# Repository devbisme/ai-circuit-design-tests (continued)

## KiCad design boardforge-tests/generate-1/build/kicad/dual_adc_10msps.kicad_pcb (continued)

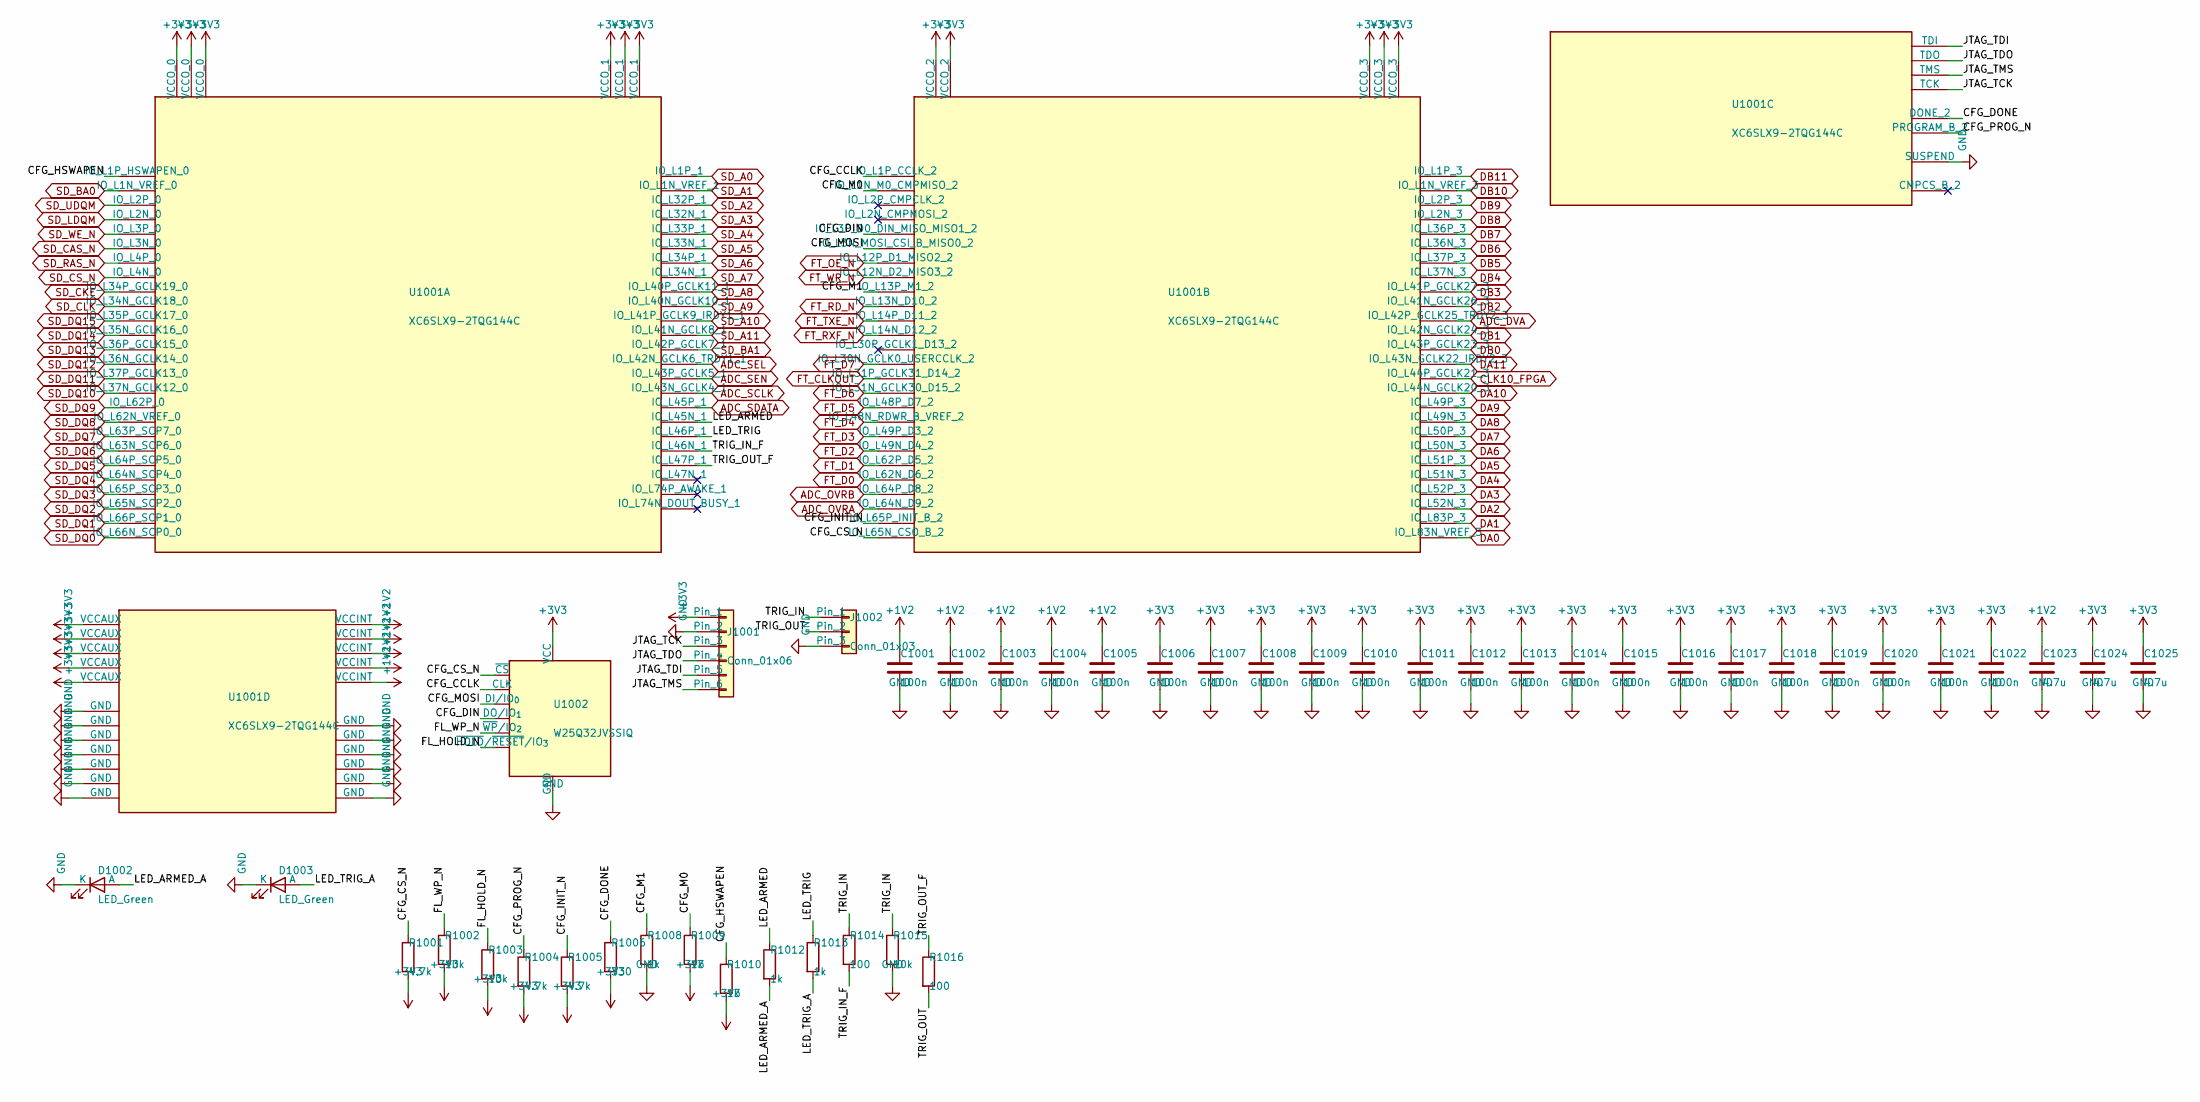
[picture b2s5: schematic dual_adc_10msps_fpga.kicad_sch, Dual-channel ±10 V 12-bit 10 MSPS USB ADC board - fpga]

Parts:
C1001, C1002, C1003, C1004, C1005, C1006, C1007, C1008, C1009, C1010, C1011, C1012, C1013, C1014, C1015, C1016, C1017, C1018, C1019, C1020, C1021, C1022: 100n; C_0402_1005Metric; MPN CL05B104KB54PNC; LCSC C307331
C1023, C1024, C1025: 4.7u; C_0603_1608Metric; MPN CL10A475KO8NNNC; LCSC C19666
D1002, D1003: LED_Green; LED_0603_1608Metric; MPN PSC-1608U52GC-G4; LCSC C22371297
J1001: Conn_01x06; PinHeader_1x06_P2.54mm_Vertical; MPN PZ254V-11-06P; LCSC C492405
J1002: Conn_01x03; PinHeader_1x03_P2.54mm_Vertical; MPN PZ254V-11-03P; LCSC C2937625
R1001, R1004, R1005: 4.7k; R_0402_1005Metric; MPN 0402WGF4701TCE; LCSC C25900
R1002, R1003, R1015: 10k; R_0402_1005Metric; MPN 0402WGF1002TCE; LCSC C25744
R1006: 330; R_0402_1005Metric; MPN 0402WGF3300TCE; LCSC C25104
R1008, R1009, R1010, R1012, R1013: 1k; R_0402_1005Metric; MPN 0402WGF1001TCE; LCSC C11702
R1014, R1016: 100; R_0402_1005Metric; MPN 0402WGF1000TCE; LCSC C25076
U1001: XC6SLX9-2TQG144C; TQFP-144_20x20mm_P0.5mm; MPN XC6SLX9-2TQG144C; LCSC C27408
U1002: W25Q32JVSSIQ; SOIC-8_5.3x5.3mm_P1.27mm; MPN W25Q32JVSSIQ; LCSC C179173

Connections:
+1V2: C1001.1, C1002.1, C1003.1, C1004.1, C1005.1, C1023.1, U1001.19 (VCCINT), U1001.28 (VCCINT), U1001.52 (VCCINT), U1001.89 (VCCINT), U1001.128 (VCCINT); also elsewhere on the board
+3V3: C1006.1, C1007.1, C1008.1, C1009.1, C1010.1, C1011.1, C1012.1, C1013.1, C1014.1, C1015.1, C1016.1, C1017.1, C1018.1, C1019.1, C1020.1, C1021.1, C1022.1, C1024.1, C1025.1, J1001.1, R1001.2, R1002.2, R1003.2, R1004.2, R1005.2, R1006.2, R1009.2, R1010.2, U1001.4 (VCCO_3), U1001.18 (VCCO_3), U1001.20 (VCCAUX), U1001.31 (VCCO_3), U1001.36 (VCCAUX), U1001.42 (VCCO_2), U1001.53 (VCCAUX), U1001.63 (VCCO_2), U1001.76 (VCCO_1), U1001.86 (VCCO_1), U1001.90 (VCCAUX), U1001.103 (VCCO_1), U1001.122 (VCCO_0), U1001.125 (VCCO_0), U1001.129 (VCCAUX), U1001.135 (VCCO_0), U1002.8 (VCC); also elsewhere on the board
/fpga/CFG_CCLK: U1001.70 (IO_L1P_CCLK_2), U1002.6 (CLK)
/fpga/CFG_CS_N: R1001.1, U1001.38 (IO_L65N_CSO_B_2), U1002.1 (~CS)
/fpga/CFG_DIN: U1001.65 (IO_L3P_D0_DIN_MISO_MISO1_2), U1002.2 (DO/IO_{1})
/fpga/CFG_DONE: R1006.1, U1001.71 (DONE_2)
/fpga/CFG_HSWAPEN: R1010.1, U1001.144 (IO_L1P_HSWAPEN_0)
/fpga/CFG_INIT_N: R1005.1, U1001.39 (IO_L65P_INIT_B_2)
/fpga/CFG_M0: R1009.1, U1001.69 (IO_L1N_M0_CMPMISO_2)
/fpga/CFG_M1: R1008.1, U1001.60 (IO_L13P_M1_2)
/fpga/CFG_MOSI: U1001.64 (IO_L3N_MOSI_CSI_B_MISO0_2), U1002.5 (DI/IO_{0})
/fpga/CFG_PROG_N: R1004.1, U1001.37 (PROGRAM_B_2)
/fpga/FL_HOLD_N: R1003.1, U1002.7 (~HOLD/~RESET/IO_{3})
/fpga/FL_WP_N: R1002.1, U1002.3 (~WP/IO_{2})
/fpga/JTAG_TCK: J1001.3, U1001.109 (TCK)
/fpga/JTAG_TDI: J1001.5, U1001.110 (TDI)
/fpga/JTAG_TDO: J1001.4, U1001.106 (TDO)
/fpga/JTAG_TMS: J1001.6, U1001.107 (TMS)
/fpga/LED_ARMED: R1012.1, U1001.82 (IO_L45N_1)
/fpga/LED_ARMED_A: D1002.2 (A), R1012.2
/fpga/LED_TRIG: R1013.1, U1001.81 (IO_L46P_1)
/fpga/LED_TRIG_A: D1003.2 (A), R1013.2
/fpga/TRIG_IN: J1002.1, R1014.1, R1015.1
/fpga/TRIG_IN_F: R1014.2, U1001.80 (IO_L46N_1)
/fpga/TRIG_OUT: J1002.2, R1016.2
/fpga/TRIG_OUT_F: R1016.1, U1001.79 (IO_L47P_1)
ADC_DVA: U1001.22 (IO_L42P_GCLK25_TRDY2_3); also elsewhere on the board
ADC_OVRA: U1001.40 (IO_L64N_D9_2); also elsewhere on the board
ADC_OVRB: U1001.41 (IO_L64P_D8_2); also elsewhere on the board
ADC_SCLK: U1001.84 (IO_L43N_GCLK4_1); also elsewhere on the board
ADC_SDATA: U1001.83 (IO_L45P_1); also elsewhere on the board
ADC_SEL: U1001.87 (IO_L42N_GCLK6_TRDY1_1); also elsewhere on the board
ADC_SEN: U1001.85 (IO_L43P_GCLK5_1); also elsewhere on the board
CLK10_FPGA: U1001.15 (IO_L44P_GCLK21_3); also elsewhere on the board
DA0: U1001.1 (IO_L83N_VREF_3); also elsewhere on the board
DA1: U1001.2 (IO_L83P_3); also elsewhere on the board
DA2: U1001.5 (IO_L52N_3); also elsewhere on the board
DA3: U1001.6 (IO_L52P_3); also elsewhere on the board
DA4: U1001.7 (IO_L51N_3); also elsewhere on the board
DA5: U1001.8 (IO_L51P_3); also elsewhere on the board
DA6: U1001.9 (IO_L50N_3); also elsewhere on the board
DA7: U1001.10 (IO_L50P_3); also elsewhere on the board
DA8: U1001.11 (IO_L49N_3); also elsewhere on the board
DA9: U1001.12 (IO_L49P_3); also elsewhere on the board
DA10: U1001.14 (IO_L44N_GCLK20_3); also elsewhere on the board
DA11: U1001.16 (IO_L43N_GCLK22_IRDY2_3); also elsewhere on the board
DB0: U1001.17 (IO_L43P_GCLK23_3); also elsewhere on the board
DB1: U1001.21 (IO_L42N_GCLK24_3); also elsewhere on the board
DB2: U1001.23 (IO_L41N_GCLK26_3); also elsewhere on the board
DB3: U1001.24 (IO_L41P_GCLK27_3); also elsewhere on the board
DB4: U1001.26 (IO_L37N_3); also elsewhere on the board
DB5: U1001.27 (IO_L37P_3); also elsewhere on the board
DB6: U1001.29 (IO_L36N_3); also elsewhere on the board
DB7: U1001.30 (IO_L36P_3); also elsewhere on the board
DB8: U1001.32 (IO_L2N_3); also elsewhere on the board
DB9: U1001.33 (IO_L2P_3); also elsewhere on the board
DB10: U1001.34 (IO_L1N_VREF_3); also elsewhere on the board
DB11: U1001.35 (IO_L1P_3); also elsewhere on the board
FT_CLKOUT: U1001.51 (IO_L31P_GCLK31_D14_2); also elsewhere on the board
FT_D0: U1001.43 (IO_L62N_D6_2); also elsewhere on the board
FT_D1: U1001.44 (IO_L62P_D5_2); also elsewhere on the board
FT_D2: U1001.45 (IO_L49N_D4_2); also elsewhere on the board
FT_D3: U1001.46 (IO_L49P_D3_2); also elsewhere on the board
FT_D4: U1001.47 (IO_L48N_RDWR_B_VREF_2); also elsewhere on the board
FT_D5: U1001.48 (IO_L48P_D7_2); also elsewhere on the board
FT_D6: U1001.50 (IO_L31N_GCLK30_D15_2); also elsewhere on the board
FT_D7: U1001.55 (IO_L30N_GCLK0_USERCCLK_2); also elsewhere on the board
FT_OE_N: U1001.62 (IO_L12P_D1_MISO2_2); also elsewhere on the board
FT_RD_N: U1001.59 (IO_L13N_D10_2); also elsewhere on the board
FT_RXF_N: U1001.57 (IO_L14N_D12_2); also elsewhere on the board
FT_TXE_N: U1001.58 (IO_L14P_D11_2); also elsewhere on the board
FT_WR_N: U1001.61 (IO_L12N_D2_MISO3_2); also elsewhere on the board
GND: C1001.2, C1002.2, C1003.2, C1004.2, C1005.2, C1006.2, C1007.2, C1008.2, C1009.2, C1010.2, C1011.2, C1012.2, C1013.2, C1014.2, C1015.2, C1016.2, C1017.2, C1018.2, C1019.2, C1020.2, C1021.2, C1022.2, C1023.2, C1024.2, C1025.2, D1002.1 (K), D1003.1 (K), J1001.2, J1002.3, R1008.2, R1015.2, U1001.3 (GND), U1001.13 (GND), U1001.25 (GND), U1001.49 (GND), U1001.54 (GND), U1001.68 (GND), U1001.73 (SUSPEND), U1001.77 (GND), U1001.91 (GND), U1001.96 (GND), U1001.108 (GND), U1001.113 (GND), U1001.130 (GND), U1001.136 (GND), U1002.4 (GND); also elsewhere on the board
SD_A0: U1001.105 (IO_L1P_1); also elsewhere on the board
SD_A1: U1001.104 (IO_L1N_VREF_1); also elsewhere on the board
SD_A2: U1001.102 (IO_L32P_1); also elsewhere on the board
SD_A3: U1001.101 (IO_L32N_1); also elsewhere on the board
SD_A4: U1001.100 (IO_L33P_1); also elsewhere on the board
SD_A5: U1001.99 (IO_L33N_1); also elsewhere on the board
SD_A6: U1001.98 (IO_L34P_1); also elsewhere on the board
SD_A7: U1001.97 (IO_L34N_1); also elsewhere on the board
SD_A8: U1001.95 (IO_L40P_GCLK11_1); also elsewhere on the board
SD_A9: U1001.94 (IO_L40N_GCLK10_1); also elsewhere on the board
SD_A10: U1001.93 (IO_L41P_GCLK9_IRDY1_1); also elsewhere on the board
SD_A11: U1001.92 (IO_L41N_GCLK8_1); also elsewhere on the board
SD_BA0: U1001.143 (IO_L1N_VREF_0); also elsewhere on the board
SD_BA1: U1001.88 (IO_L42P_GCLK7_1); also elsewhere on the board
SD_CAS_N: U1001.139 (IO_L3N_0); also elsewhere on the board
SD_CKE: U1001.134 (IO_L34P_GCLK19_0); also elsewhere on the board
SD_CLK: U1001.133 (IO_L34N_GCLK18_0); also elsewhere on the board
SD_CS_N: U1001.137 (IO_L4N_0); also elsewhere on the board
SD_DQ0: U1001.111 (IO_L66N_SCP0_0); also elsewhere on the board
SD_DQ1: U1001.112 (IO_L66P_SCP1_0); also elsewhere on the board
SD_DQ2: U1001.114 (IO_L65N_SCP2_0); also elsewhere on the board
SD_DQ3: U1001.115 (IO_L65P_SCP3_0); also elsewhere on the board
SD_DQ4: U1001.116 (IO_L64N_SCP4_0); also elsewhere on the board
SD_DQ5: U1001.117 (IO_L64P_SCP5_0); also elsewhere on the board
SD_DQ6: U1001.118 (IO_L63N_SCP6_0); also elsewhere on the board
SD_DQ7: U1001.119 (IO_L63P_SCP7_0); also elsewhere on the board
SD_DQ8: U1001.120 (IO_L62N_VREF_0); also elsewhere on the board
SD_DQ9: U1001.121 (IO_L62P_0); also elsewhere on the board
SD_DQ10: U1001.123 (IO_L37N_GCLK12_0); also elsewhere on the board
SD_DQ11: U1001.124 (IO_L37P_GCLK13_0); also elsewhere on the board
SD_DQ12: U1001.126 (IO_L36N_GCLK14_0); also elsewhere on the board
SD_DQ13: U1001.127 (IO_L36P_GCLK15_0); also elsewhere on the board
SD_DQ14: U1001.131 (IO_L35N_GCLK16_0); also elsewhere on the board
SD_DQ15: U1001.132 (IO_L35P_GCLK17_0); also elsewhere on the board
SD_LDQM: U1001.141 (IO_L2N_0); also elsewhere on the board
SD_RAS_N: U1001.138 (IO_L4P_0); also elsewhere on the board
SD_UDQM: U1001.142 (IO_L2P_0); also elsewhere on the board
SD_WE_N: U1001.140 (IO_L3P_0); also elsewhere on the board

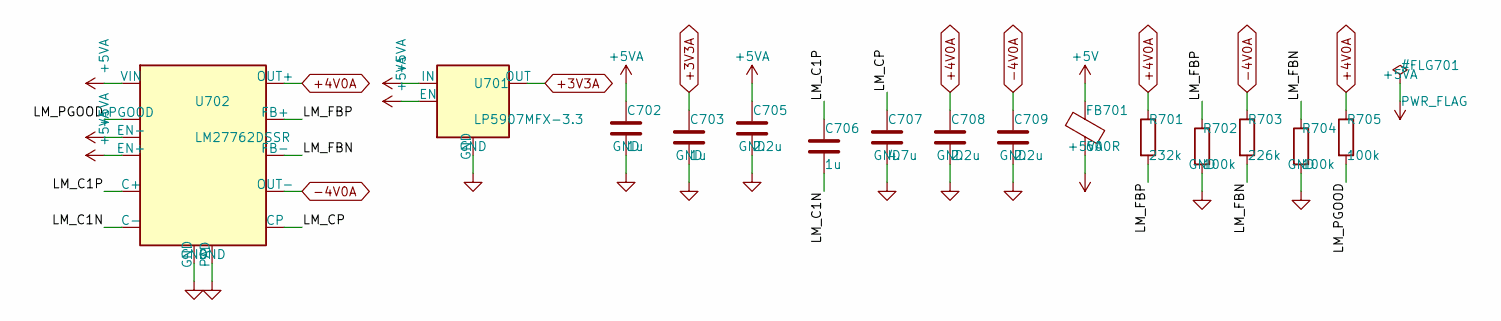
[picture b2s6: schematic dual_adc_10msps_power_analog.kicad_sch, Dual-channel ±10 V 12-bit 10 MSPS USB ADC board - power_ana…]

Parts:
C702, C703, C706: 1u; C_0402_1005Metric; MPN CL05A105KA5NQNC; LCSC C52923
C705, C708, C709: 2.2u; C_0603_1608Metric; MPN CL10A225KO8NNNC; LCSC C23630
C707: 4.7u; C_0603_1608Metric; MPN CL10A475KO8NNNC; LCSC C19666
FB701: 600R; L_0603_1608Metric; MPN BLM18KG601SN1D; LCSC C85833
R701: 232k; R_0402_1005Metric; MPN FRC0402F2323TS; LCSC C3013159
R702, R704, R705: 100k; R_0402_1005Metric; MPN 0402WGF1003TCE; LCSC C25741
R703: 226k; R_0402_1005Metric; MPN FRC0402F2263TS; LCSC C5121518
U701: LP5907MFX-3.3; SOT-23-5; MPN LP5907MFX-3.3/NOPB; LCSC C80670
U702: LM27762DSSR; WSON-12-1EP_3x2mm_P0.5mm_EP1x2.65; MPN LM27762DSSR; LCSC C473398

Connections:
+3V3A: C703.1, U701.5 (OUT); also elsewhere on the board
+4V0A: C708.1, R701.1, R705.1, U702.11 (OUT+); also elsewhere on the board
+5V: FB701.1; also elsewhere on the board
+5VA: C702.1, C705.1, FB701.2, U701.1 (IN), U701.3 (EN), U702.3 (VIN), U702.8 (EN-), U702.12 (EN+)
-4V0A: C709.1, R703.1, U702.6 (OUT-); also elsewhere on the board
/power_analog/LM_C1N: C706.2, U702.9 (C-)
/power_analog/LM_C1P: C706.1, U702.10 (C+)
/power_analog/LM_CP: C707.1, U702.5 (CP)
/power_analog/LM_FBN: R703.2, R704.1, U702.7 (FB-)
/power_analog/LM_FBP: R701.2, R702.1, U702.2 (FB+)
/power_analog/LM_PGOOD: R705.2, U702.1 (PGOOD)
GND: C702.2, C703.2, C705.2, C707.2, C708.2, C709.2, R702.2, R704.2, U701.2 (GND), U702.4 (GND), U702.13 (PAD); also elsewhere on the board

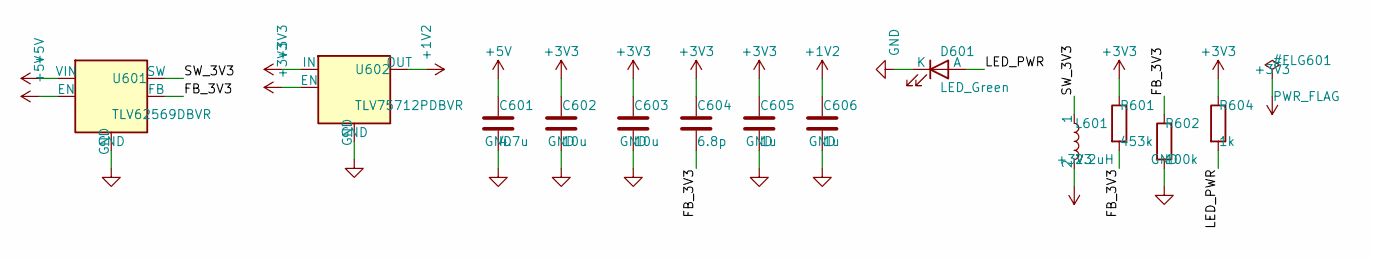
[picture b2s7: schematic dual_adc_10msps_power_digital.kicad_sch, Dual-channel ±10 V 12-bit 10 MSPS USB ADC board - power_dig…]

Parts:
C601: 4.7u; C_0603_1608Metric; MPN CL10A475KO8NNNC; LCSC C19666
C602, C603: 10u; C_0603_1608Metric; MPN CL10A106KP8NNNC; LCSC C19702
C604: 6.8p; C_0402_1005Metric; MPN 0402CG6R8C500NT; LCSC C1576
C605, C606: 1u; C_0402_1005Metric; MPN CL05A105KA5NQNC; LCSC C52923
D601: LED_Green; LED_0603_1608Metric; MPN PSC-1608U52GC-G4; LCSC C22371297
L601: 2.2uH; L_1008_2520Metric; MPN TMS252012ALM-2R2MTAA; LCSC C1017131
R601: 453k; R_0402_1005Metric; MPN 0402WGF4533TCE; LCSC C27009
R602: 100k; R_0402_1005Metric; MPN 0402WGF1003TCE; LCSC C25741
R604: 1k; R_0402_1005Metric; MPN 0402WGF1001TCE; LCSC C11702
U601: TLV62569DBVR; SOT-23-5; MPN TLV62569DBVR; LCSC C141836
U602: TLV75712PDBVR; SOT-23-5; MPN TLV75712PDBVR; LCSC C1509296

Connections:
+1V2: C606.1, U602.5 (OUT); also elsewhere on the board
+3V3: C602.1, C603.1, C604.1, C605.1, L601.2, R601.1, R604.1, U602.1 (IN), U602.3 (EN); also elsewhere on the board
+5V: C601.1, U601.1 (EN), U601.4 (VIN); also elsewhere on the board
/power_digital/FB_3V3: C604.2, R601.2, R602.1, U601.5 (FB)
/power_digital/LED_PWR: D601.2 (A), R604.2
/power_digital/SW_3V3: L601.1, U601.3 (SW)
GND: C601.2, C602.2, C603.2, C605.2, C606.2, D601.1 (K), R602.2, U601.2 (GND), U602.2 (GND); also elsewhere on the board

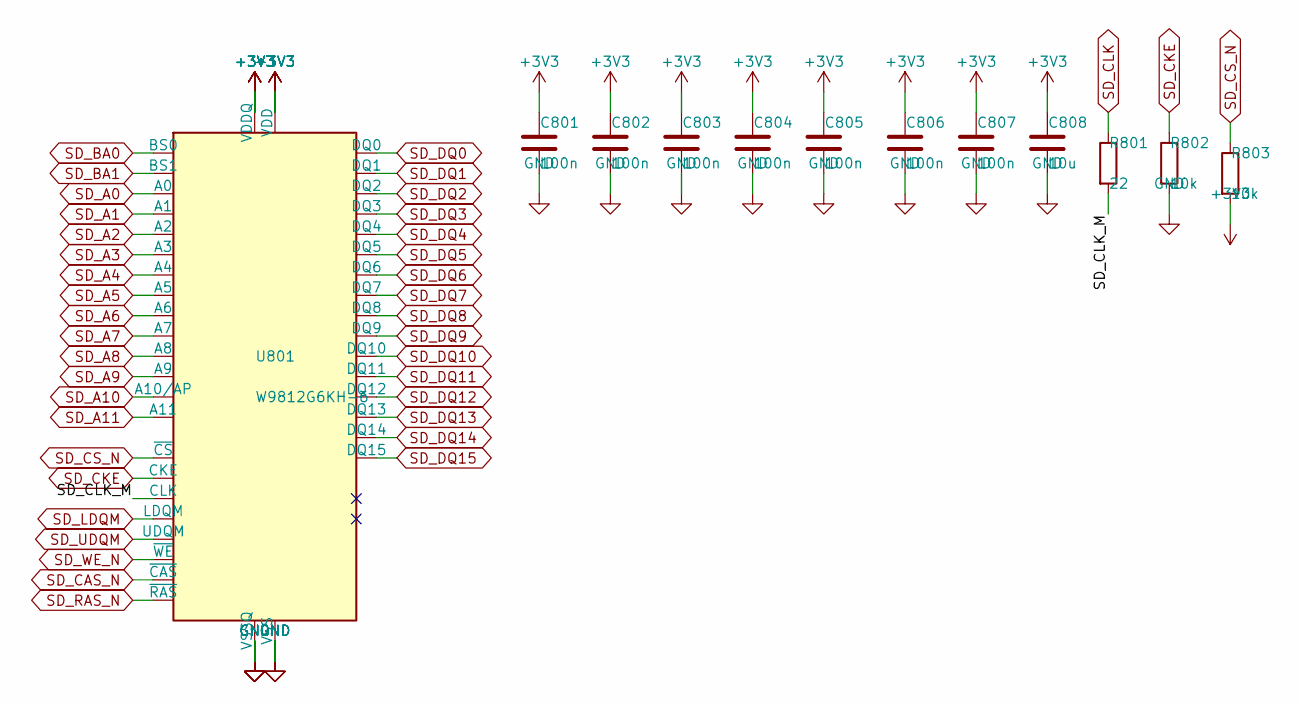
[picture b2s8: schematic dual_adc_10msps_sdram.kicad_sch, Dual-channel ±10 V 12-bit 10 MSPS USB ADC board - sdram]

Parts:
C801, C802, C803, C804, C805, C806, C807: 100n; C_0402_1005Metric; MPN CL05B104KB54PNC; LCSC C307331
C808: 10u; C_0603_1608Metric; MPN CL10A106KP8NNNC; LCSC C19702
R801: 22; R_0402_1005Metric; MPN 0402WGF220JTCE; LCSC C25092
R802, R803: 10k; R_0402_1005Metric; MPN 0402WGF1002TCE; LCSC C25744
U801: W9812G6KH-6; TSOP-II-54_22.2x10.16mm_P0.8mm; MPN W9812G6KH-6; LCSC C62379

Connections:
+3V3: C801.1, C802.1, C803.1, C804.1, C805.1, C806.1, C807.1, C808.1, R803.2, U801.1 (VDD), U801.3 (VDDQ), U801.9 (VDDQ), U801.14 (VDD), U801.27 (VDD), U801.43 (VDDQ), U801.49 (VDDQ); also elsewhere on the board
/sdram/SD_CLK_M: R801.2, U801.38 (CLK)
GND: C801.2, C802.2, C803.2, C804.2, C805.2, C806.2, C807.2, C808.2, R802.2, U801.6 (VSSQ), U801.12 (VSSQ), U801.28 (VSS), U801.41 (VSS), U801.46 (VSSQ), U801.52 (VSSQ), U801.54 (VSS); also elsewhere on the board
SD_A0: U801.23 (A0); also elsewhere on the board
SD_A1: U801.24 (A1); also elsewhere on the board
SD_A2: U801.25 (A2); also elsewhere on the board
SD_A3: U801.26 (A3); also elsewhere on the board
SD_A4: U801.29 (A4); also elsewhere on the board
SD_A5: U801.30 (A5); also elsewhere on the board
SD_A6: U801.31 (A6); also elsewhere on the board
SD_A7: U801.32 (A7); also elsewhere on the board
SD_A8: U801.33 (A8); also elsewhere on the board
SD_A9: U801.34 (A9); also elsewhere on the board
SD_A10: U801.22 (A10/AP); also elsewhere on the board
SD_A11: U801.35 (A11); also elsewhere on the board
SD_BA0: U801.20 (BS0); also elsewhere on the board
SD_BA1: U801.21 (BS1); also elsewhere on the board
SD_CAS_N: U801.17 (~CAS); also elsewhere on the board
SD_CKE: R802.1, U801.37 (CKE); also elsewhere on the board
SD_CLK: R801.1; also elsewhere on the board
SD_CS_N: R803.1, U801.19 (~CS); also elsewhere on the board
SD_DQ0: U801.2 (DQ0); also elsewhere on the board
SD_DQ1: U801.4 (DQ1); also elsewhere on the board
SD_DQ2: U801.5 (DQ2); also elsewhere on the board
SD_DQ3: U801.7 (DQ3); also elsewhere on the board
SD_DQ4: U801.8 (DQ4); also elsewhere on the board
SD_DQ5: U801.10 (DQ5); also elsewhere on the board
SD_DQ6: U801.11 (DQ6); also elsewhere on the board
SD_DQ7: U801.13 (DQ7); also elsewhere on the board
SD_DQ8: U801.42 (DQ8); also elsewhere on the board
SD_DQ9: U801.44 (DQ9); also elsewhere on the board
SD_DQ10: U801.45 (DQ10); also elsewhere on the board
SD_DQ11: U801.47 (DQ11); also elsewhere on the board
SD_DQ12: U801.48 (DQ12); also elsewhere on the board
SD_DQ13: U801.50 (DQ13); also elsewhere on the board
SD_DQ14: U801.51 (DQ14); also elsewhere on the board
SD_DQ15: U801.53 (DQ15); also elsewhere on the board
SD_LDQM: U801.15 (LDQM); also elsewhere on the board
SD_RAS_N: U801.18 (~RAS); also elsewhere on the board
SD_UDQM: U801.39 (UDQM); also elsewhere on the board
SD_WE_N: U801.16 (~WE); also elsewhere on the board

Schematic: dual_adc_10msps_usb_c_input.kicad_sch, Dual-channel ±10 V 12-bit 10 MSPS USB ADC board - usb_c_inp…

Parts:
C501: 1u; C_0402_1005Metric; MPN CL05A105KA5NQNC; LCSC C52923
D501: SMF5.0A; D_SOD-123F; MPN SMF5.0A; LCSC C19077497
F501: 750mA; Fuse_1812_4532Metric; MPN JK-mSMD075-33; LCSC C369169
J501: TYPE-C-31-M-12; USB_C_Receptacle_HRO_TYPE-C-31-M-12; MPN TYPE-C-31-M-12; LCSC C165948
R501, R502: 5.1k; R_0402_1005Metric; MPN 0402WGF5101TCE; LCSC C25905
U501: USBLC6-2SC6; SOT-23-6; MPN USBLC6-2SC6; LCSC C7519

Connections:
+5V: F501.2; also elsewhere on the board
/usb_c_input/CC1: J501.A5 (CC1), R501.1
/usb_c_input/CC2: J501.B5 (CC2), R502.1
GND: C501.2, D501.2 (A2), J501.A1 (GND), J501.A12 (GND), J501.B1 (GND), J501.B12 (GND), J501.SH (SHIELD), R501.2, R502.2, U501.2 (GND); also elsewhere on the board
USB_DM: J501.A7 (D-), J501.B7 (D-), U501.3 (I/O2), U501.4 (I/O2); also elsewhere on the board
USB_DP: J501.A6 (D+), J501.B6 (D+), U501.1 (I/O1), U501.6 (I/O1); also elsewhere on the board
VBUS: C501.1, D501.1 (A1), F501.1, J501.A4 (VBUS), J501.A9 (VBUS), J501.B4 (VBUS), J501.B9 (VBUS), U501.5 (VBUS)

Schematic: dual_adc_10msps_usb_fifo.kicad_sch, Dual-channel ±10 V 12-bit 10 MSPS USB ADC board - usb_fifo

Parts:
C901, C902: 18p; C_0402_1005Metric; MPN 0402CG180J500NT; LCSC C1549
C903, C909: 4.7u; C_0603_1608Metric; MPN CL10A475KO8NNNC; LCSC C19666
C904, C905, C906, C907, C908, C910, C911, C912, C913: 100n; C_0402_1005Metric; MPN CL05B104KB54PNC; LCSC C307331
FB901: 600R; L_0603_1608Metric; MPN BLM18KG601SN1D; LCSC C85833
R901: 12k; R_0402_1005Metric; MPN 0402WGF1202TCE; LCSC C25752
R902, R904, R905, R906, R907, R908, R909, R911, R912: 10k; R_0402_1005Metric; MPN 0402WGF1002TCE; LCSC C25744
R903: 2.2k; R_0402_1005Metric; MPN 0402WGF2201TCE; LCSC C25879
R910: 22; R_0402_1005Metric; MPN 0402WGF220JTCE; LCSC C25092
U901: FT232HL; LQFP-48_7x7mm_P0.5mm; MPN FT232HL; LCSC C51997
U902: 93LC56BT-I/OT; SOT-23-6; MPN 93LC56BT-I/OT; LCSC C190271
Y901: 12MHz; Crystal_SMD_2520-4Pin_2.5x2.0mm; MPN TXM12M0004252FBCEO00T; LCSC C284155

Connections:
+3V3: C906.1, C907.1, C908.1, C909.1, C910.1, C913.1, FB901.1, R902.2, R904.2, R905.2, R906.2, R907.2, R908.2, R909.2, R911.2, R912.2, U901.12 (VCCIO), U901.24 (VCCIO), U901.39 (VCCD), U901.40 (VREGIN), U901.46 (VCCIO), U902.6 (VCC); also elsewhere on the board
/usb_fifo/+3V3_PHY: C903.1, C904.1, C905.1, FB901.2, U901.3 (VPHY), U901.8 (VPLL)
/usb_fifo/EE_CLK: R905.1, U901.44 (EECLK), U902.4 (CLK)
/usb_fifo/EE_CS: R904.1, U901.45 (EECS), U902.5 (CS)
/usb_fifo/EE_DATA: R903.2, R906.1, U901.43 (EEDATA), U902.3 (DI)
/usb_fifo/EE_DO: R903.1, U902.1 (DO)
/usb_fifo/FT_CLKOUT_S: R910.1, U901.29 (ACBUS5)
/usb_fifo/FT_PWRSAV_N: R912.1, U901.31 (ACBUS7)
/usb_fifo/FT_REF: R901.1, U901.5 (REF)
/usb_fifo/FT_RESET_N: R902.1, U901.34 (~RESET)
/usb_fifo/FT_SIWU_N: R909.1, U901.28 (ACBUS4)
/usb_fifo/FT_VCCA: C912.1, U901.37 (VCCA)
/usb_fifo/FT_VCORE: C911.1, U901.38 (VCCCORE)
/usb_fifo/FT_XI: C901.1, U901.1 (XCSI), Y901.1
/usb_fifo/FT_XO: C902.1, U901.2 (XCSO), Y901.3
FT_CLKOUT: R910.2; also elsewhere on the board
FT_D0: U901.13 (ADBUS0); also elsewhere on the board
FT_D1: U901.14 (ADBUS1); also elsewhere on the board
FT_D2: U901.15 (ADBUS2); also elsewhere on the board
FT_D3: U901.16 (ADBUS3); also elsewhere on the board
FT_D4: U901.17 (ADBUS4); also elsewhere on the board
FT_D5: U901.18 (ADBUS5); also elsewhere on the board
FT_D6: U901.19 (ADBUS6); also elsewhere on the board
FT_D7: U901.20 (ADBUS7); also elsewhere on the board
FT_OE_N: R911.1, U901.30 (ACBUS6); also elsewhere on the board
FT_RD_N: R907.1, U901.26 (ACBUS2); also elsewhere on the board
FT_RXF_N: U901.21 (ACBUS0); also elsewhere on the board
FT_TXE_N: U901.25 (ACBUS1); also elsewhere on the board
FT_WR_N: R908.1, U901.27 (ACBUS3); also elsewhere on the board
GND: C901.2, C902.2, C903.2, C904.2, C905.2, C906.2, C907.2, C908.2, C909.2, C910.2, C911.2, C912.2, C913.2, R901.2, U901.4 (AGND), U901.9 (AGND), U901.10 (GND), U901.11 (GND), U901.22 (GND), U901.23 (GND), U901.35 (GND), U901.36 (GND), U901.41 (AGND), U901.42 (TEST), U901.47 (GND), U901.48 (GND), U902.2 (GND), Y901.2 (G), Y901.4 (G); also elsewhere on the board
USB_DM: U901.6 (DM); also elsewhere on the board
USB_DP: U901.7 (DP); also elsewhere on the board

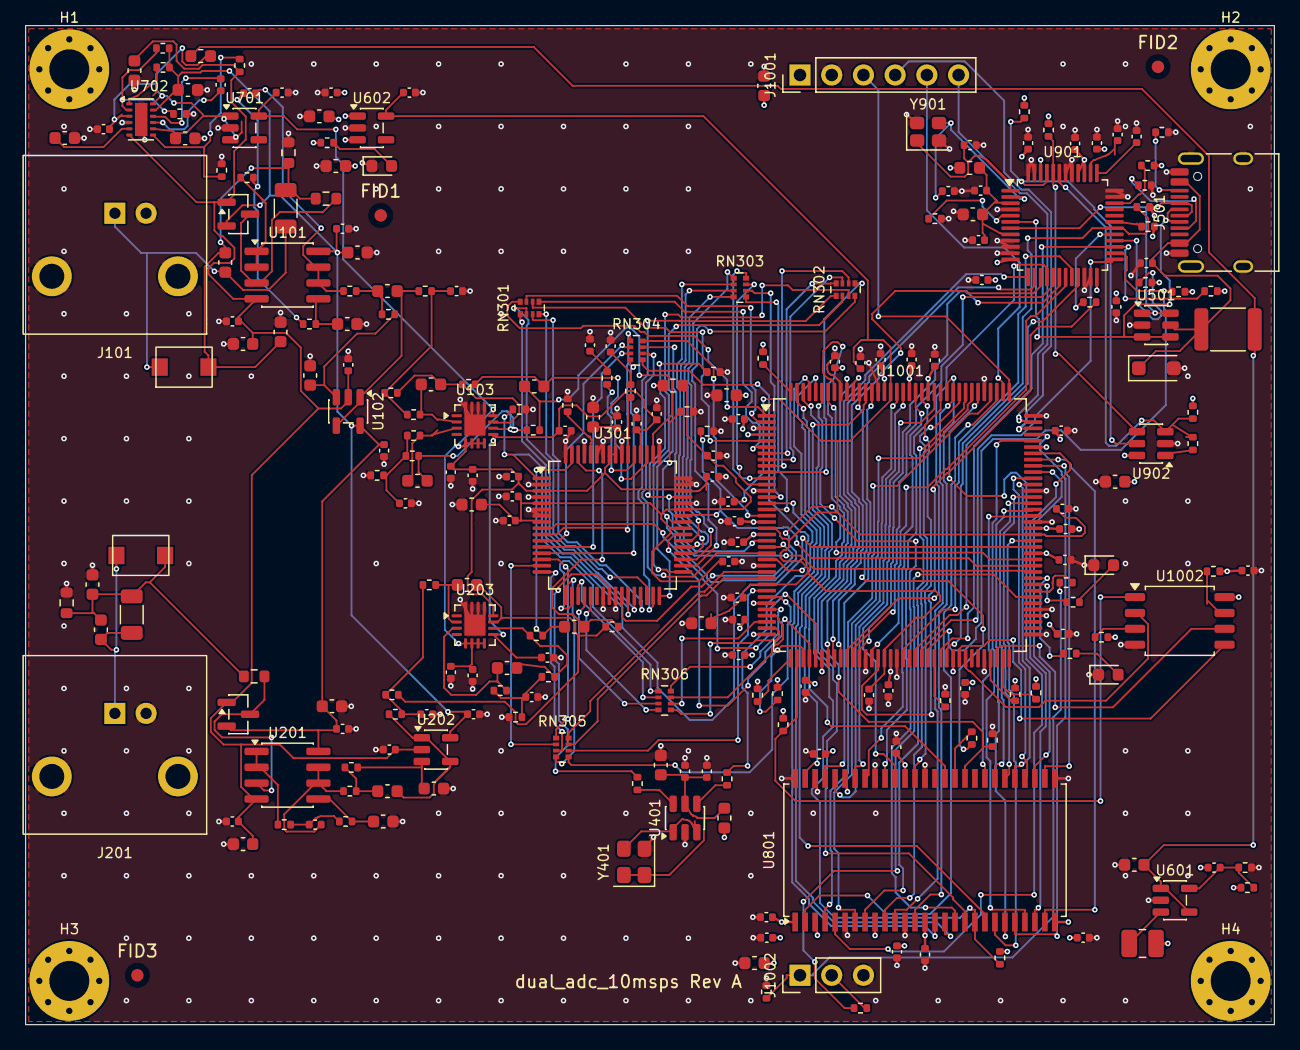
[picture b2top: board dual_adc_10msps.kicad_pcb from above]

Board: 4 copper layers, 100.0 x 80.0 mm, 246 parts (0 on the bottom side), 217 nets.

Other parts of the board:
FID1, FID2, FID3: Fiducial; Fiducial_1mm_Mask2mm
H1, H2, H3, H4: MountingHole; MountingHole_3.2mm_M3_Pad_Via

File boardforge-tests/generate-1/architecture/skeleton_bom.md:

# Skeleton BOM — dual_adc_10msps (per board; qty 5 boards)

Passive defaults unless noted: resistors 0402 1 % thick film; decoupling 0.1 µF 0402 X7R
16 V; bulk X5R ≥ 10 V. Filter caps = C0G/NP0 **≤ ±2 %** (±1 % preferred; ±5 % keeps the HARD
stopband but SOFT flatness p99 rises to ~1 dB). AFE refs: channel A 1xx, channel B 2xx
(same values; qty column counts both channels).

## ICs, connectors, critical parts

| Function | Suggested MPN | Package | Qty | Refs | Notes |
|---|---|---|---|---|---|
| Dual 12-bit 40 MSPS ADC | ADS5231IPAGT | TQFP-64 10×10 | 1 | U301 | Critical; symbol to generate; C2670079 (152 stk) |
| FPGA | XC6SLX9-2TQG144C | TQFP-144 20×20 | 1 | U1001 | Critical; symbol FPGA_Xilinx_Spartan6:XC6SLX4-TQG144 |
| SPI config flash 32 Mbit | W25Q32JVSSIQ | SOIC-8 208 mil | 1 | U1002 | Any SPI NOR ≥ 4 Mbit supported by Spartan-6 |
| SDRAM 16 MB ×16 | W9812G6KH-6 | TSOP-II-54 | 1 | U801 | 2nd source W9825G6KH-6 (32 MB, pin 36 = A12) |
| USB HS FIFO bridge | FT232HL | LQFP-48 7×7 | 1 | U901 | Critical (sync FIFO) |
| EEPROM for FT232H | 93LC56BT-I/OT | SOT-23-6 | 1 | U902 | 16-bit org ("B") mandatory |
| Crystal 12 MHz | 12 MHz ±30 ppm, CL 8–12 pF | 3225 | 1 | Y901 | Load caps C901/C902 = 2 × (CL − 3 pF) |
| Dual FET op-amp | OPA2810IDR | SOIC-8 | 2 | U101, U201 | Buffer + SK_a |
| FET op-amp | OPA810IDBVR | SOT-23-5 | 2 | U102, U202 | SK_b (Q 2.28) — GBW 70 MHz is designed in |
| FDA | THS4551IRGTR | VQFN-16 3×3 | 2 | U103, U203 | FB± pins NC |
| Clamp diode pair | BAV199 | SOT-23 | 2 | D101, D201 | Low-leakage series pair |
| BNC female, right angle, 50 Ω, PCB | KH-BNC50-3511 | THT | 2 | J101, J201 | Through-hole (no SMD BNC) |
| Trimmer cap 2–6 pF 100 V | STC3MA06-T1 | SMD 4.5×3.2 | 2 | C102, C202 | Probe-comp trim; SPICE value "3.3p" (nominal setting) |
| ±4 V low-noise charge pump | LM27762DSSR | WSON-12 | 1 | U702 | |
| 3.3 V LDO analog | LP5907MFX-3.3/NOPB | SOT-23-5 | 1 | U701 | Cout total ≤ 10 µF |
| 3.3 V buck 2 A | TLV62569DBVR | SOT-23-5 | 1 | U601 | |
| 1.2 V LDO 1 A | TLV75712PDBVR | SOT-23-5 | 1 | U602 | |
| 10 MHz CMOS XO 3.3 V | SX3M10.000B10F20TNN | 3225 | 1 | Y401 | Jitter ≤ 5 ps rms |
| Dual buffer | SN74LVC2G34DBVR | SOT-23-6 | 1 | U401 | |
| USB-C receptacle USB2.0 16P | TYPE-C-31-M-12 | SMD | 1 | J501 | Symbol Connector:USB_C_Receptacle_USB2.0_16P |
| USB ESD | USBLC6-2SC6 | SOT-23-6 | 1 | U501 | |
| VBUS TVS 5 V | SMF5.0A | SOD-123F | 1 | D501 | |
| PTC fuse 0.75 A hold | e.g. SMD1206P075TF | 1206 | 1 | F501 | R ≤ 0.3 Ω |
| Ferrite 600 Ω@100 MHz, ≥ 0.5 A | e.g. GZ1608D601TF | 0603 | 4 | FB301, FB401, FB701, FB901 | FB701 carries ~0.15 A; DCR ≤ 0.15 Ω |
| Inductor 2.2 µH ≥ 1.5 A Isat | e.g. 4×4 mm shielded | SMD | 1 | L601 | |
| 33 Ω ×4 resistor array | 4D02WGJ0330TCE | 0402×4 | 6 | RN301–RN306 | ADC output series R |
| JTAG header 1×6 2.54 mm | generic | THT | 1 | J1001 | Digilent HS2 order |
| Trigger header 1×3 2.54 mm | generic | THT | 1 | J1002 | |
| LED green (power), 2× user | 0603 | 0603 | 3 | D601, D1002, D1003 | |

## AFE passives (×2 channels; refs for A, B = +100)

| Function | Value | Package | Qty | Refs (A) | Notes |
|---|---|---|---|---|---|
| Attenuator top R | 953 kΩ 1 % | **1206** (200 V) | 2 | R101 | sees 28.5 V at ±30 V input |
| Attenuator top C | 8.2 pF C0G **100 V** ±0.25 pF | 0603 | 2 | C101 | |
| Attenuator bottom R | 49.9 kΩ 1 % | 0603 | 2 | R102 | |
| Attenuator bottom C | 220 pF C0G ±5 % | 0603 | 2 | C103 | trim absorbs tolerance |
| Input series R | 1.00 kΩ | 0603 | 2 | R103 | |
| SK_a R1 / R2 | 887 Ω / 453 Ω | 0402 | 4 | R104 / R105 | |
| SK_a C1 (fb) / C2 (gnd) | 270 pF / 100 pF C0G ≤2 % | 0402/0603 | 4 | C104 / C105 | |
| SK_b R1 / R2 | 374 Ω / 232 Ω | 0402 | 4 | R106 / R107 | |
| SK_b C1 (fb) / C2 (gnd) | 1.8 nF / 82 pF C0G ≤2 % | 0603 | 4 | C106 / C107 | |
| MFB R1 (×2 sides) | 698 Ω | 0402 | 4 | R108, R109 | |
| MFB R2 (×2) | 1.27 kΩ | 0402 | 4 | R110, R111 | gain 1270/698 = 1.8195 |
| MFB R3 (×2) | 576 Ω | 0402 | 4 | R112, R113 | |
| MFB C1 (×2, to GND) | 330 pF C0G ≤2 % | 0402 | 4 | C108, C109 | |
| MFB C2 (×2, feedback) | 82 pF C0G ≤2 % | 0402 | 4 | C110, C111 | |
| ADC RC series R (×2) | 46.4 Ω | 0402 | 4 | R114, R115 | |
| ADC RC diff C | 1.2 nF C0G ≤2 % | 0603 | 2 | C112 | |
| Op-amp decoupling | 0.1 µF | 0402 | 8 | C113–C116 | |
| FDA decoupling | 0.1 µF + 1 µF | 0402 | 4 | C117, C118 | |
| VOCM bypass | 10 nF | 0402 | 2 | C119 | |
| ±4V0A local bulk | 2.2 µF 10 V | 0603 | 4 | C120, C121 | |

## Other blocks — passives

| Block | Refs | Values |
|---|---|---|
| usb_c_input | R501, R502; C501 | 5.1 kΩ 1 % ×2; 1 µF 10 V |
| power_digital | C601; C602, C603; R601; R602; C604; C605, C606; R604 | 4.7 µF 10 V; 10 µF 10 V ×2; 453 kΩ 1 %; 100 kΩ 1 %; 6.8 pF C0G; 1 µF ×2; 1 kΩ |
| power_analog | C702, C703; C705, C708, C709; C706; C707; R701; R702, R704; R703 | 1 µF ×2; 2.2 µF ×3; 1 µF (flying); 4.7 µF; 232 kΩ 1 %; 100 kΩ 1 % ×2; 226 kΩ 1 % |
| adc | R301; R302, R303; C301, C302; C303; C304; C305–C307; C308; C309–C312; C313; R304–R307 | 56.2 kΩ 1 %; 2.0 Ω ×2; 0.1 µF ×2; 0.1 µF; 1 µF; 0.1 µF ×3; 4.7 µF; 0.1 µF ×4; 4.7 µF; 10 kΩ ×4 |
| clock | C401, C402; C403; R401, R402 | 0.1 µF ×2; 4.7 µF; 33 Ω ×2 |
| sdram | C801–C807; C808; R801; R802, R803 | 0.1 µF ×7; 10 µF; 22 Ω; 10 kΩ ×2 |
| usb_fifo | C901, C902; R901; R902, R904–R909, R911, R912; R903; R910; C903, C909; C904–C908, C910–C913 | 18 pF C0G (per crystal CL) ×2; 12.0 kΩ 1 %; 10 kΩ ×10; 2.2 kΩ; 22 Ω; 4.7 µF ×2; 0.1 µF ×9 |
| fpga | R1001, R1004, R1005; R1002, R1003, R1015; R1006; R1008–R1010; R1012, R1013; R1014, R1016; C1001–C10nn | 4.7 kΩ ×3; 10 kΩ ×3; 330 Ω; 1 kΩ ×3; 1 kΩ ×2; 100 Ω ×2; 0.1 µF one per VCCINT/VCCAUX/VCCO pin (+ U1002) + 4.7 µF ×3 bulk (coder counts pins from the symbol) |

Cost estimate (qty 5, parts only): ICs ≈ $70 (ADC 29.8, FPGA 7.4, SDRAM 6.1, FT232H 9.5,
op-amps/FDAs 21, power 1.5, misc 3), connectors/trimmers ≈ $4, passives ≈ $6 → ≈ $80/board
+ JLC extended-part fees (≈ 30 unique × $3 per order, ≈ $18/board at qty 5) → ≈ $100 ≤ $150 SOFT.
